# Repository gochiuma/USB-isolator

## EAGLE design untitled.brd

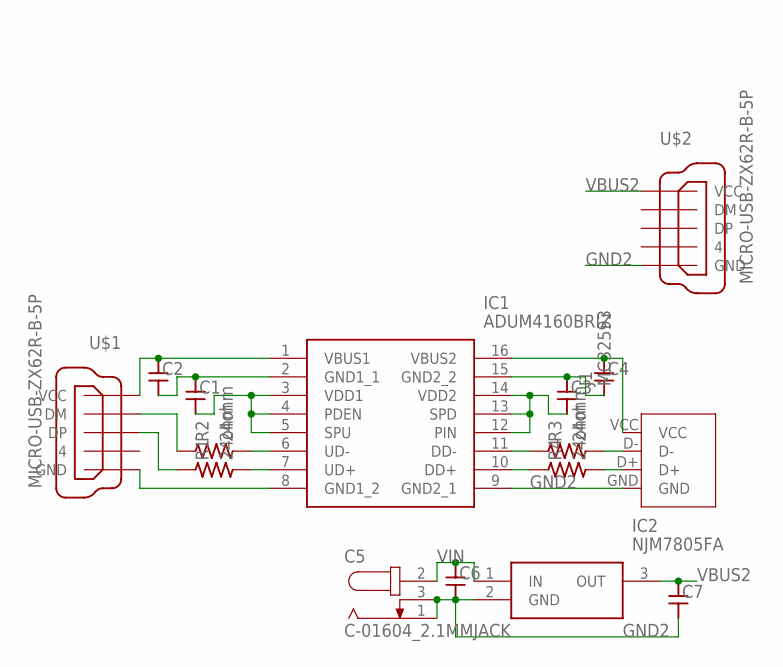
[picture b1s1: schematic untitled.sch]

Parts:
C1, C2, C3, C4, C6, C7: CAPACITOR2012; SMD2012
C5: C-01604_2.1MMJACK; 2.1MMJACK
IC1: ADUM4160BRIZ; SOIC127P1032X265-16N
IC2: NJM7805FA; TO254P500X1000X2170-3P
J1: MC32593
R1, R2, R3, R4: 24ohm; SMD1608
U$1, U$2: MICRO-USB-ZX62R-B-5P; ZX62R-B-5P

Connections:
D+M: J1.D+, R4.2
D-M: J1.D-, R3.2
DD+: IC1.10 (DD+), R4.1
DD-: IC1.11 (DD-), R3.1
DM: R2.1, U$1.2 (DM)
DP: R1.1, U$1.3 (DP)
GND1: C1.1, C2.2, IC1.2 (GND1_1), IC1.8 (GND1_2), U$1.5 (GND)
GND2: C3.1, C4.2, C5.1 (GND), C5.3 (S), C6.2, C7.2, IC1.9 (GND2_1), IC1.15 (GND2_2), IC2.2 (GND), J1.GND, U$2.5 (GND)
unnamed: C3.2, IC1.12 (PIN), IC1.13 (SPD), IC1.14 (VDD2)
UD+: IC1.7 (UD+), R1.2
UD-: IC1.6 (UD-), R2.2
VBUS1: C2.1, IC1.1 (VBUS1), U$1.1 (VCC)
VBUS2: C4.1, C7.1, IC1.16 (VBUS2), IC2.3 (OUT), J1.VCC, U$2.1 (VCC)
VDD1: C1.2, IC1.3 (VDD1), IC1.4 (PDEN), IC1.5 (SPU)
VIN: C5.2 (VCC), C6.1, IC2.1 (IN)

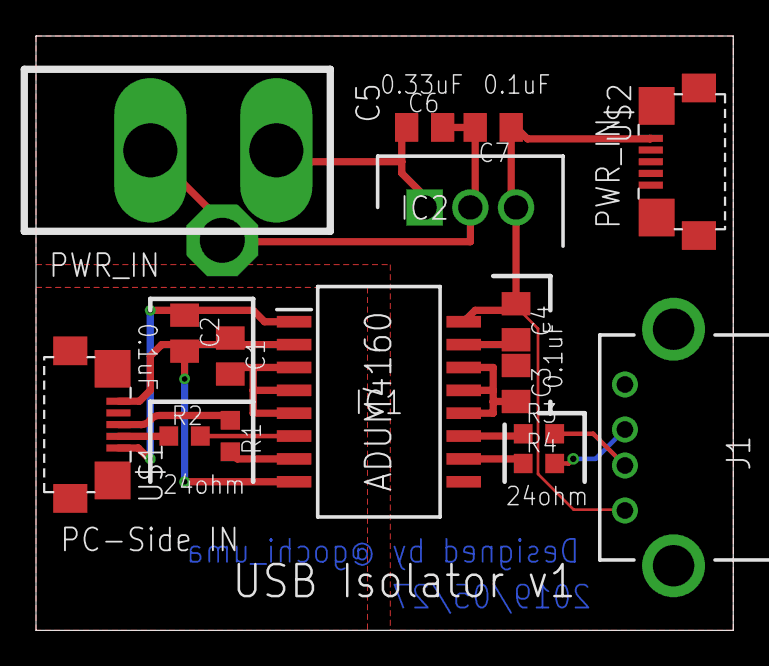
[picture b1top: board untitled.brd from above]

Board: 2 copper layers, 38.7 x 33.0 mm, 16 parts (0 on the bottom side), 15 nets.

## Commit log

2019-12-14 USB-microB iso
